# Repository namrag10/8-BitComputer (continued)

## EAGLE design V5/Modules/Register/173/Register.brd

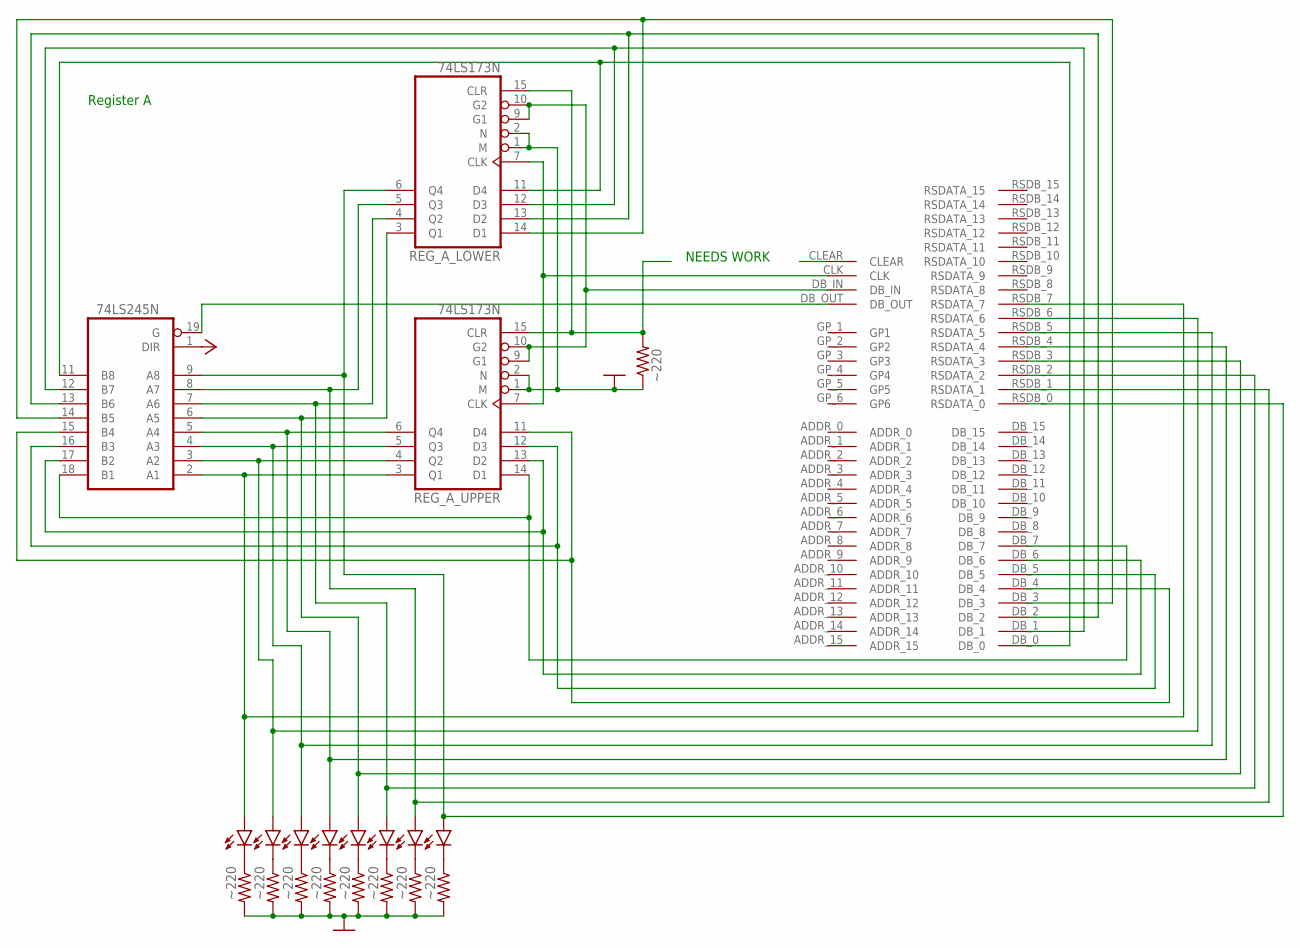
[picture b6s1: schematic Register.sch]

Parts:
LED_A_REG_1, LED_A_REG_2, LED_A_REG_3, LED_A_REG_4, LED_A_REG_5, LED_A_REG_6, LED_A_REG_7, LED_A_REG_8: LED; LED5MM
OUTPUT_BUFFER_REG_A: 74LS245N; DIL20
R1, R2, R3, R4, R5, R6, R7, R8, R9: ~220; 0204/7
REG_A_LOWER: 74LS173N; DIL16
REG_A_UPPER: 74LS173N; DIL16
U$1: BACKPLATE_INTERFACE; BACK_INTERFACE-FOOT

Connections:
1_PLACE1: OUTPUT_BUFFER_REG_A.11 (B8), REG_A_LOWER.11 (D4), U$1.DB_0
2_PLACE: OUTPUT_BUFFER_REG_A.12 (B7), REG_A_LOWER.12 (D3), U$1.DB_1
4_PLACE: OUTPUT_BUFFER_REG_A.13 (B6), REG_A_LOWER.13 (D2), U$1.DB_2
8_PLACE: OUTPUT_BUFFER_REG_A.14 (B5), REG_A_LOWER.14 (D1), U$1.DB_3
16_PLACE: OUTPUT_BUFFER_REG_A.15 (B4), REG_A_UPPER.11 (D4), U$1.DB_4
32_PLACE: OUTPUT_BUFFER_REG_A.16 (B3), REG_A_UPPER.12 (D3), U$1.DB_5
64_PLACE: OUTPUT_BUFFER_REG_A.17 (B2), REG_A_UPPER.13 (D2), U$1.DB_6
128_PLACE: OUTPUT_BUFFER_REG_A.18 (B1), REG_A_UPPER.14 (D1), U$1.DB_7
CLOCK: REG_A_LOWER.7 (CLK), REG_A_UPPER.7 (CLK), U$1.CLK
GND: OUTPUT_BUFFER_REG_A.10 (GND), R1.2, R2.2, R3.2, R4.2, R5.2, R6.2, R7.2, R8.2, R9.1, REG_A_LOWER.1 (M), REG_A_LOWER.2 (N), REG_A_LOWER.8 (GND), REG_A_UPPER.1 (M), REG_A_UPPER.2 (N), REG_A_UPPER.8 (GND), U$1.GND, U$1.GND2 (GND)
IN_SIGNAL: REG_A_LOWER.9 (G1), REG_A_LOWER.10 (G2), REG_A_UPPER.9 (G1), REG_A_UPPER.10 (G2), U$1.DB_IN
unnamed: LED_A_REG_1.K (C), R1.1
unnamed: R9.2, REG_A_LOWER.15 (CLR), REG_A_UPPER.15 (CLR)
unnamed: LED_A_REG_2.K (C), R2.1
unnamed: LED_A_REG_3.K (C), R3.1
unnamed: LED_A_REG_4.K (C), R4.1
unnamed: LED_A_REG_5.K (C), R5.1
unnamed: LED_A_REG_6.K (C), R6.1
unnamed: LED_A_REG_7.K (C), R7.1
unnamed: LED_A_REG_8.K (C), R8.1
OUT_SIGNAL: OUTPUT_BUFFER_REG_A.19 (G), U$1.DB_OUT
REG_A_1PLACE: LED_A_REG_1.A, OUTPUT_BUFFER_REG_A.9 (A8), REG_A_LOWER.6 (Q4), U$1.RSDB_0 (RSDATA_0)
REG_A_2PLACE: LED_A_REG_2.A, OUTPUT_BUFFER_REG_A.8 (A7), REG_A_LOWER.5 (Q3), U$1.RSDB_1 (RSDATA_1)
REG_A_4PLACE: LED_A_REG_3.A, OUTPUT_BUFFER_REG_A.7 (A6), REG_A_LOWER.4 (Q2), U$1.RSDB_2 (RSDATA_2)
REG_A_8PLACE: LED_A_REG_4.A, OUTPUT_BUFFER_REG_A.6 (A5), REG_A_LOWER.3 (Q1), U$1.RSDB_3 (RSDATA_3)
REG_A_16PLACE: LED_A_REG_5.A, OUTPUT_BUFFER_REG_A.5 (A4), REG_A_UPPER.6 (Q4), U$1.RSDB_4 (RSDATA_4)
REG_A_32PLACE: LED_A_REG_6.A, OUTPUT_BUFFER_REG_A.4 (A3), REG_A_UPPER.5 (Q3), U$1.RSDB_5 (RSDATA_5)
REG_A_64PLACE: LED_A_REG_7.A, OUTPUT_BUFFER_REG_A.3 (A2), REG_A_UPPER.4 (Q2), U$1.RSDB_6 (RSDATA_6)
REG_A_128PLACE: LED_A_REG_8.A, OUTPUT_BUFFER_REG_A.2 (A1), REG_A_UPPER.3 (Q1), U$1.RSDB_7 (RSDATA_7)
VCC: OUTPUT_BUFFER_REG_A.1 (DIR), OUTPUT_BUFFER_REG_A.20 (VCC), REG_A_LOWER.16 (VCC), REG_A_UPPER.16 (VCC), U$1.VCC, U$1.VCC2 (VCC)

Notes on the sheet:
Register A
NEEDS WORK

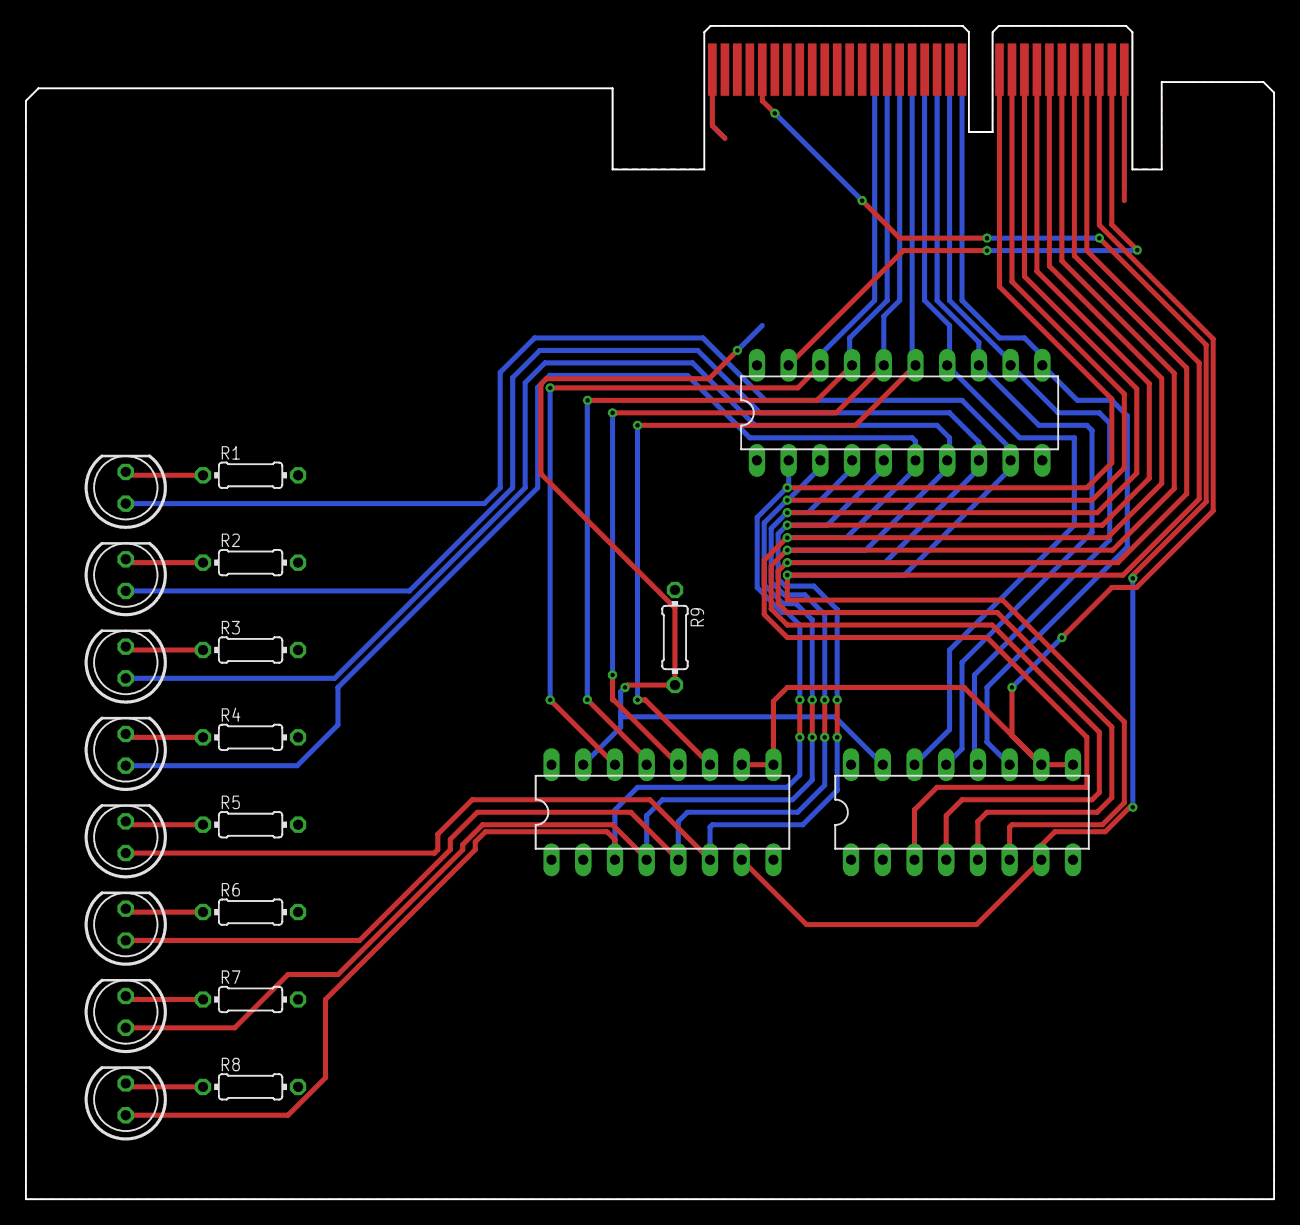
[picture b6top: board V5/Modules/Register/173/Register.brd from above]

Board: 2 copper layers, 100.0 x 94.0 mm, 21 parts (0 on the bottom side), 30 nets.
